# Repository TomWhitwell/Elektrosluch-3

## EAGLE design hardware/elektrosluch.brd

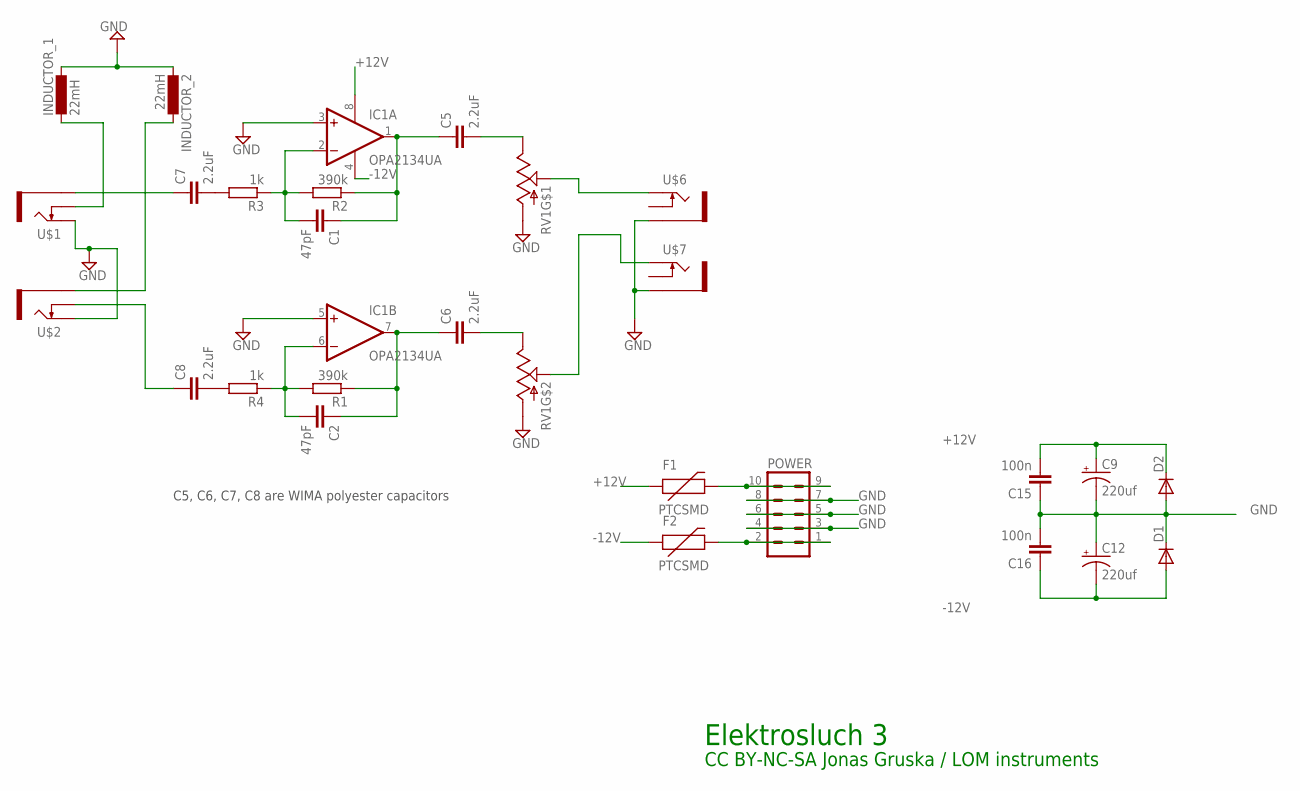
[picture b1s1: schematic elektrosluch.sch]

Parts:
C1, C2: 47pF; C0805
C5, C6, C7, C8: 2.2uF; WIMA10UF
C9, C12: 220uf; CPOL-RADIAL-10UF-25V
C15, C16: 100n; R0805
D1, D2: DIODE-SOD123; SOD123
F1, F2: PTCSMD; PTC-1206
IC1: OPA2134UA; SO08
INDUCTOR_1, INDUCTOR_2: 22mH; COIL
POWER: 10_PIN_HEADER; MA05-2
R1, R2: 390k; R0805
R3, R4: 1k; R0805
RV1: POT_DUAL; POT_PANASONIC_DUAL_VERT_KIT
U$1, U$2, U$6, U$7: THONKICONNNEW; WQP-PJ301M-12_JACK

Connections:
+12V: C9.1 (+), C15.2, D2.C, F1.1, IC1.8 (V+)
-12V: C12.2 (-), C16.1, D1.A, F2.1, IC1.4 (V-)
GND: C9.2 (-), C12.1 (+), C15.1, C16.2, D1.C, D2.A, IC1.3 (+IN), IC1.5 (+IN), INDUCTOR_1.P$1 (1), INDUCTOR_2.P$2 (2), POWER.3, POWER.4, POWER.5, POWER.6, POWER.7, POWER.8, RV1.A3 (A), RV1.B3 (A), U$1.P$1_TIP (TIP), U$2.P$1_TIP (TIP), U$6.P$3_SLEEVE (SLEEVE), U$7.P$3_SLEEVE (SLEEVE)
unnamed: C1.2, IC1.2 (-IN), R2.2, R3.1
unnamed: C1.1, C5.P$1 (1), IC1.1 (OUT), R2.1
unnamed: C5.P$2 (2), RV1.A1 (E)
unnamed: C2.2, IC1.6 (-IN), R1.2, R4.1
unnamed: C2.1, C6.P$1 (1), IC1.7 (OUT), R1.1
unnamed: C6.P$2 (2), RV1.B1 (E)
unnamed: RV1.A2 (S), U$6.P$1_TIP (TIP)
unnamed: C7.P$1 (1), U$1.P$3_SLEEVE (SLEEVE)
unnamed: RV1.B2 (S), U$7.P$1_TIP (TIP)
unnamed: C8.P$1 (1), U$2.P$2_SWITCH (SWITCH)
unnamed: C7.P$2 (2), R3.2
unnamed: INDUCTOR_1.P$2 (2), U$1.P$2_SWITCH (SWITCH)
unnamed: INDUCTOR_2.P$1 (1), U$2.P$3_SLEEVE (SLEEVE)
unnamed: F1.2, POWER.9, POWER.10
unnamed: C8.P$2 (2), R4.2
unnamed: F2.2, POWER.1, POWER.2

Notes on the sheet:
Elektrosluch 3
CC BY-NC-SA Jonas Gruska / LOM instruments
C5, C6, C7, C8 are WIMA polyester capacitors

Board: 2 copper layers, 27 parts (0 on the bottom side), 19 nets, no tracks yet.

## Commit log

2016-09-22 Layout tests

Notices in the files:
parts and their libraries:
SparkFun-Electromechanical: Licensing: CC v3.0 Share-Alike You are welcome to use this library for commercial purposes.
